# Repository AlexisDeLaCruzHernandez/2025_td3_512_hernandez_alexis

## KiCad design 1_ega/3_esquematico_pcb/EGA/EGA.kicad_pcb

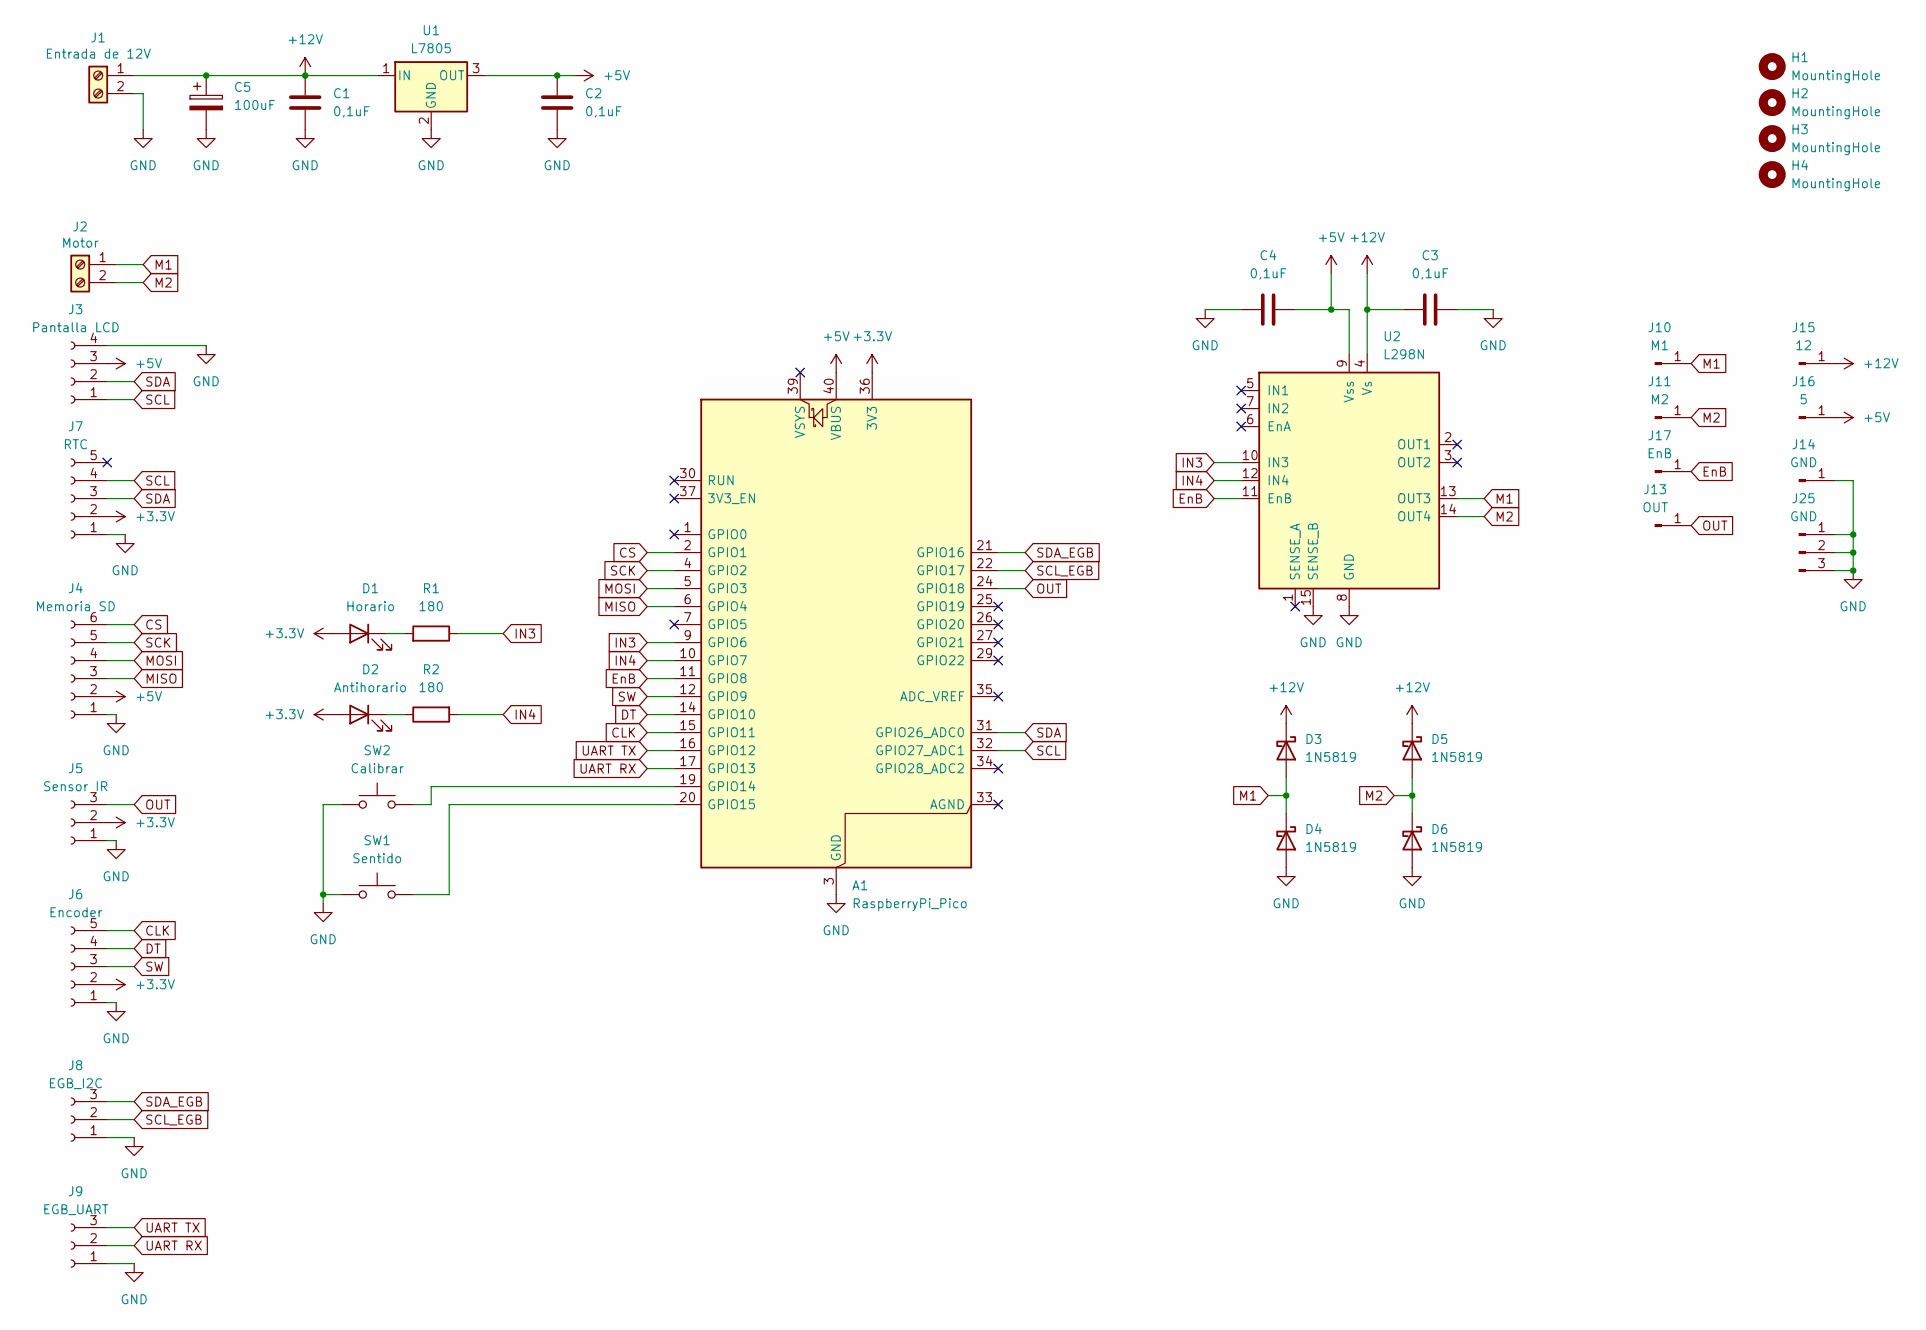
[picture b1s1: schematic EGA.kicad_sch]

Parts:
A1: RaspberryPi_Pico; RaspberryPi_Pico_Common_THT_mod
C1, C2, C3, C4: 0,1uF; C_Disc_D3.0mm_W2.0mm_P2.50mm
C5: 100uF; CP_Radial_D7.5mm_P2.50mm
D1: Horario; LED_D5.0mm
D2: Antihorario; LED_D5.0mm
D3, D4, D5, D6: 1N5819; D_DO-41_SOD81_P10.16mm_Horizontal
H1, H2, H3, H4: MountingHole; MountingHole_3mm
J1: Entrada de 12V; TerminalBlock_Phoenix_MKDS-1,5-2-5.08_1x02_P5.08mm_Horizont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
J2: Motor; TerminalBlock_Phoenix_MKDS-1,5-2-5.08_1x02_P5.08mm_Horizont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
J3: Pantalla LCD; PinSocket_1x04_P2.54mm_Vertical
J4: Memoria SD; PinSocket_1x06_P2.54mm_Vertical
J5: Sensor IR; PinSocket_1x03_P2.54mm_Vertical
J6: Encoder; PinSocket_1x05_P2.54mm_Vertical
J7: RTC; PinSocket_1x05_P2.54mm_Vertical
J8: EGB_I2C; PinSocket_1x03_P2.54mm_Vertical
J9: EGB_UART; PinSocket_1x03_P2.54mm_Vertical
J10: M1; PinHeader_1x01_P2.54mm_Vertical
J11: M2; PinHeader_1x01_P2.54mm_Vertical
J13: OUT; PinHeader_1x01_P2.54mm_Vertical
J14: GND; PinHeader_1x01_P2.54mm_Vertical
J15: 12; PinHeader_1x01_P2.54mm_Vertical
J16: 5; PinHeader_1x01_P2.54mm_Vertical
J17: EnB; PinHeader_1x01_P2.54mm_Vertical
J25: GND; PinHeader_1x03_P2.54mm_Vertical
R1, R2: 180; R_Axial_DIN0207_L6.3mm_D2.5mm_P10.16mm_Horizontal
SW1: Sentido; SW_PUSH_6mm
SW2: Calibrar; SW_PUSH_6mm
U1: L7805; TO-220-3_Vertical
U2: L298N; TO-220-15_P2.54x5.08mm_StaggerOdd_Lead4.58mm_Vertical

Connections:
+3.3V: A1.36 (3V3), D1.2 (A), D2.2 (A), J5.2, J6.2, J7.2
+5V: A1.40 (VBUS), C2.2, C4.2, J3.3, J4.2, J16.1, U1.3 (OUT), U2.9 (Vss)
+12V: C1.1, C3.1, C5.1, D3.1 (K), D5.1 (K), J1.1, J15.1, U1.1 (IN), U2.4 (Vs)
CLK: A1.15 (GPIO11), J6.5
CS: A1.2 (GPIO1), J4.6
DT: A1.14 (GPIO10), J6.4
EnB: A1.11 (GPIO8), J17.1, U2.11 (EnB)
GND: A1.3 (GND), A1.8 (GND), A1.13 (GND), A1.18 (GND), A1.23 (GND), A1.28 (GND), A1.38 (GND), C1.2, C2.1, C3.2, C4.1, C5.2, D4.2 (A), D6.2 (A), J1.2, J3.4, J4.1, J5.1, J6.1, J7.1, J8.1, J9.1, J14.1, J25.1, J25.2, J25.3, SW1.2, SW2.2, U1.2 (GND), U2.8 (GND), U2.15 (SENSE_B)
IN3: A1.9 (GPIO6), R1.1, U2.10 (IN3)
IN4: A1.10 (GPIO7), R2.2, U2.12 (IN4)
M1: D3.2 (A), D4.1 (K), J2.1, J10.1, U2.13 (OUT3)
M2: D5.2 (A), D6.1 (K), J2.2, J11.1, U2.14 (OUT4)
MISO: A1.6 (GPIO4), J4.3
MOSI: A1.5 (GPIO3), J4.4
unnamed: A1.19 (GPIO14), SW2.1
unnamed: A1.20 (GPIO15), SW1.1
unnamed: D1.1 (K), R1.2
unnamed: D2.1 (K), R2.1
OUT: A1.24 (GPIO18), J5.3, J13.1
SCK: A1.4 (GPIO2), J4.5
SCL: A1.32 (GPIO27_ADC1), J3.1, J7.4
SCL_EGB: A1.22 (GPIO17), J8.2
SDA: A1.31 (GPIO26_ADC0), J3.2, J7.3
SDA_EGB: A1.21 (GPIO16), J8.3
SW: A1.12 (GPIO9), J6.3
UART RX: A1.17 (GPIO13), J9.2
UART TX: A1.16 (GPIO12), J9.3

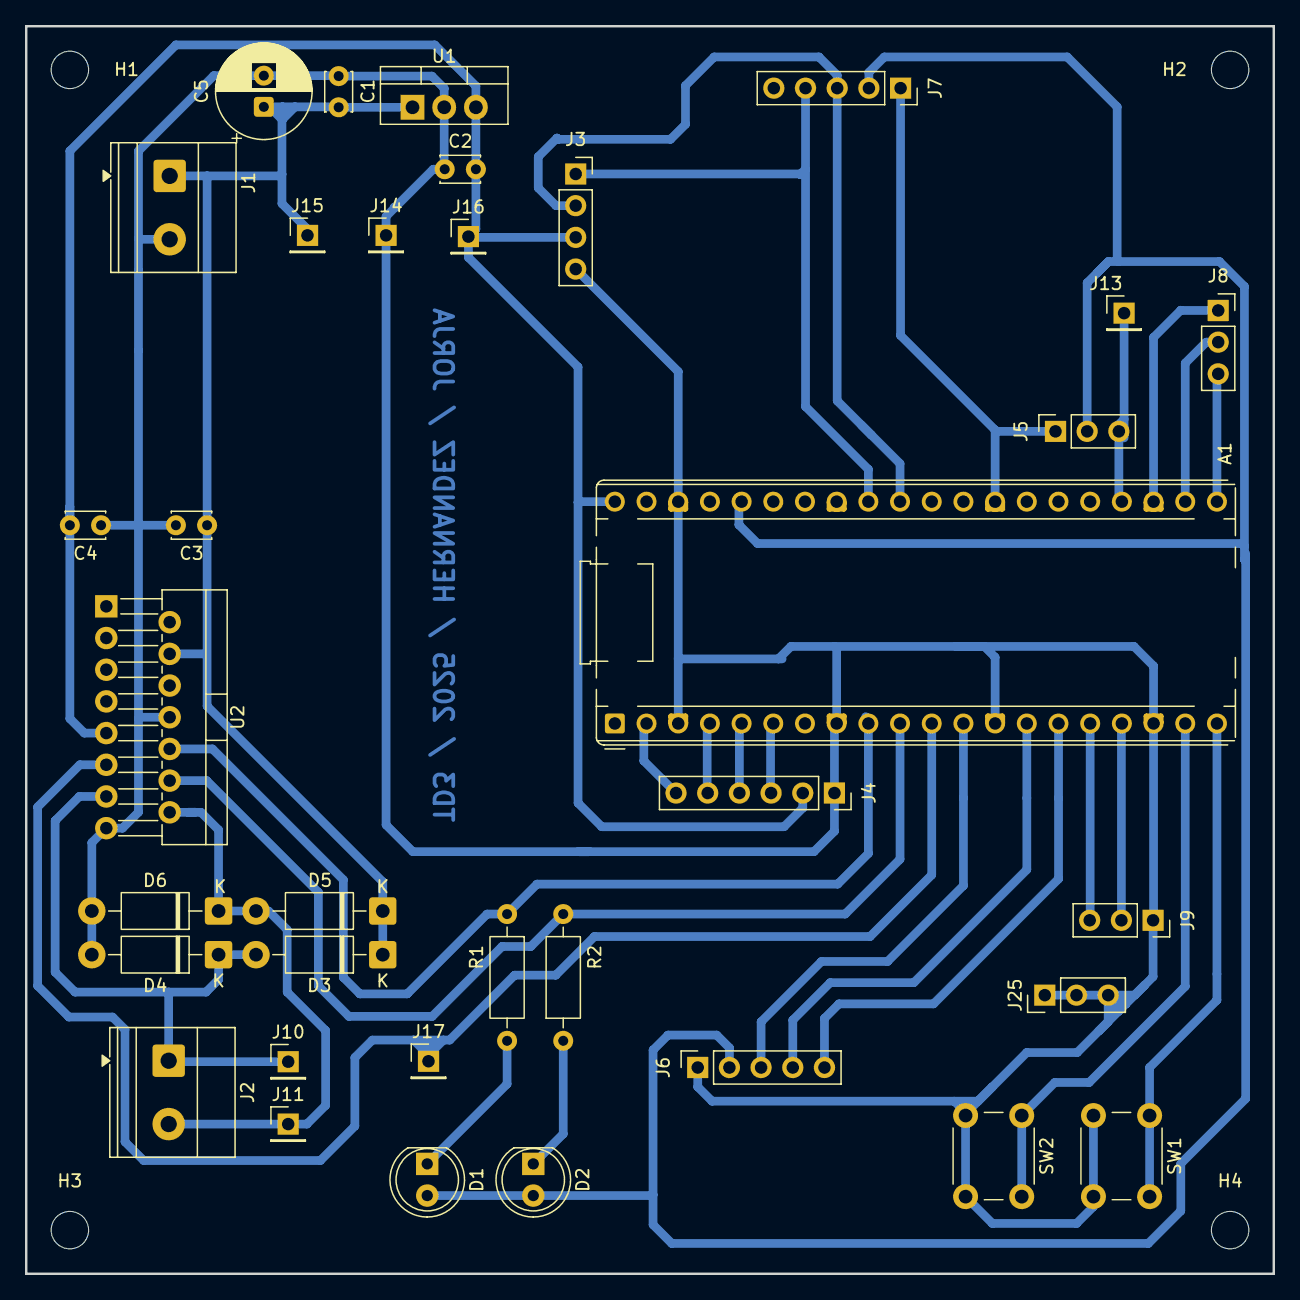
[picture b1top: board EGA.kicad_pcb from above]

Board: 2 copper layers, 100.0 x 100.0 mm, 39 parts (0 on the bottom side), 27 nets.

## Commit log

2025-05-12 Solución de error cambio de rama
2025-05-26 Primer consigna de TP2
2025-05-26 Segunda consigna de TP2
2025-06-02 Primer consigna de TP3
2025-06-03 Segunda consigna de TP3
2025-06-13 Primer consigna de TP4
2025-06-23 Segunda consigna de TP4
2025-06-23 Guía de código
2025-07-02 Diagrama en bloques tentativo
2025-07-15 Cambios en el diagrama en bloques
2025-07-15 Librerias y codigo de pruebas
2025-07-15 Esquematico y diseño de PCB
2025-08-04 Version 1.0
2025-08-09 Diagrama en bloques final
2025-08-09 Codigo final
2025-08-09 Archivo de KiCad final
2025-08-09 Esquematico final
2025-08-09 Diseño de PCB final
2025-08-09 Solucionado error de fecha y sentido
2025-08-09 Solucionado error al reconectar la SD
2025-08-10 Cambio en R1 y R2
2025-08-10 Diagrama de tareas
2025-08-10 Modelos 3D finales
2025-08-10 Datasheets
2025-08-10 Cuestionario Teorico
2025-08-11 Se añadió el link al video
2025-08-11 Informe del proyecto
2025-08-11 Link a video actualizado
2025-08-11 Se actualizó el link al video en referencias
2025-08-20 Se añadió pie de pagina con numero de hoja
2025-09-15 Error en merge
2025-09-29 Primer consigna de TP5
2025-09-30 Segunda consigna de TP5
2025-10-26 Agregado char device con fops
2025-10-26 Makefile
2025-10-26 dev-tree uart
2025-10-27 Arreglos para compilar
2025-11-01 Ya funciona con UART usando echo
2025-11-01 Eliminado dts viejo
2025-11-03 Arreglada comunicacion con user space
2025-11-03 Aplicacion de usuario por consola
2025-11-09 Solucion a mensajes basura de la pico
2025-11-09 Solucionado formato de la fecha
2025-11-09 Agregado velocidad objetivo 0
2025-11-09 Codigo EGA modificado
2025-11-09 Arreglados errores
2025-11-15 Solucionado error de lectura
2025-11-15 Envio final de respuesta
2025-11-15 Solucion envio de fecha y estetica
2025-11-15 App web
2025-11-16 Lista de comandos añadida
2025-11-16 Se añade la guia de usuario para el uso de la web
2025-11-16 Diagrama en bloques EGB
2025-11-16 Diagrama de tareas EGB
2025-11-16 Diagrama de software EGB
2025-11-16 Informe
2025-11-17 Cuestionario teorico añadido
2025-11-17 Añadidos videos del funcionamiento
2025-11-17 Actualizadas las referencias
